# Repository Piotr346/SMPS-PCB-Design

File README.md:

# SMPS-PCB-Design
Switch-mode power supply design

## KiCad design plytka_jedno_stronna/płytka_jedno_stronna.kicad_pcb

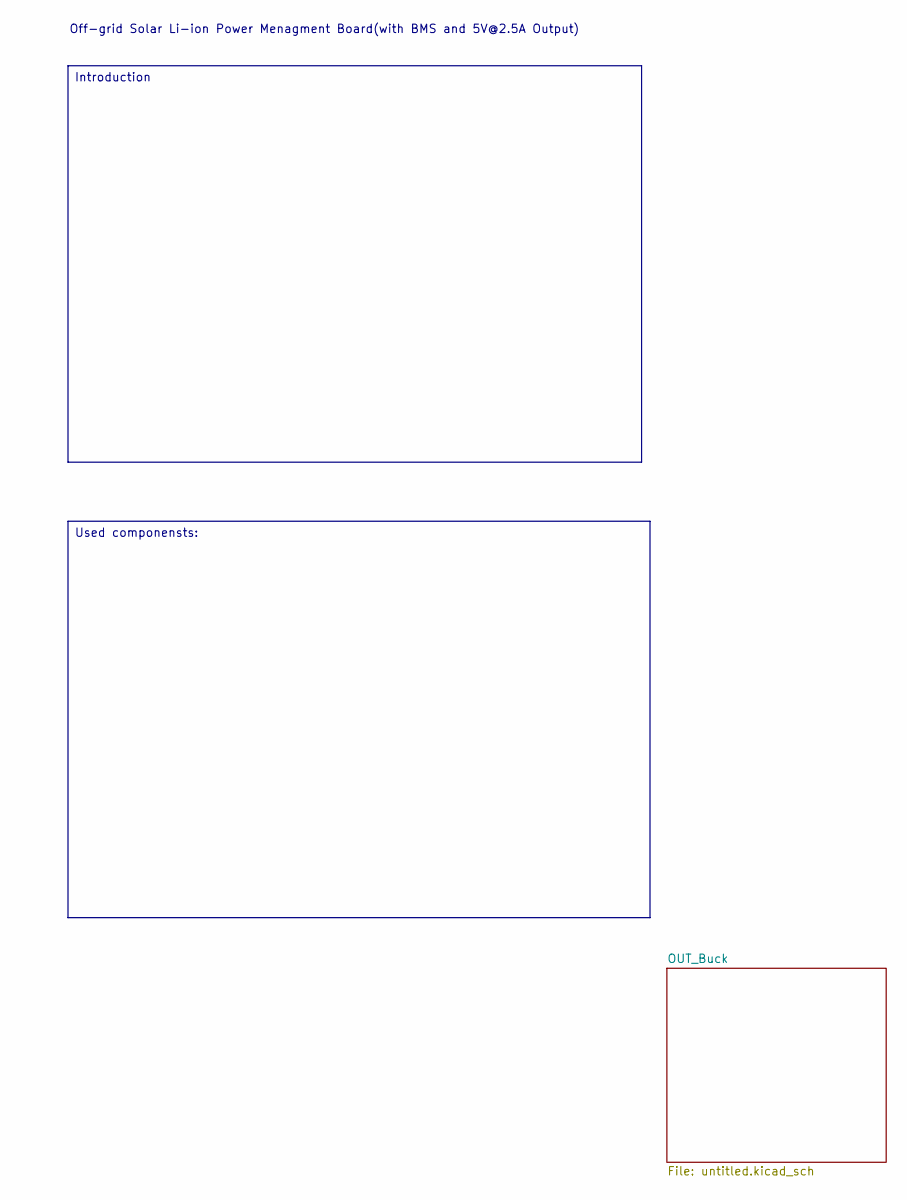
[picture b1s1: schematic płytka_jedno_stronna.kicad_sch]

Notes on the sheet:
Off-grid Solar Li-ion Power Menagment Board(with BMS and 5V@2.5A Output)
Introduction
Used componensts:

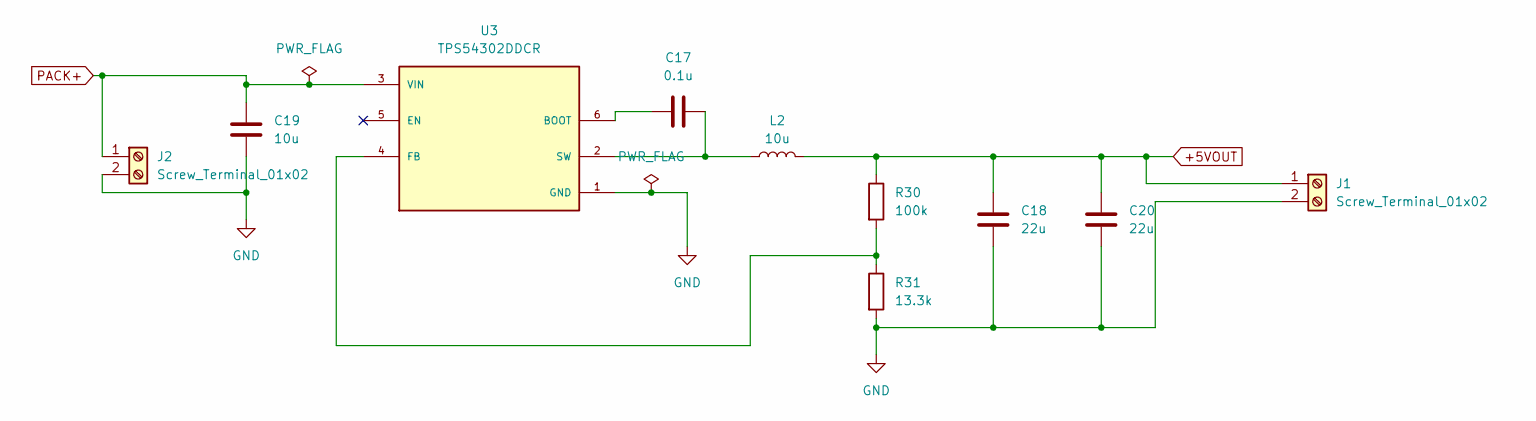
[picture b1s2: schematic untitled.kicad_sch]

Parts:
C17: 0.1u; C_1206_3216Metric_Pad1.33x1.80mm_HandSolder
C18, C20: 22u; C_1206_3216Metric_Pad1.33x1.80mm_HandSolder
C19: 10u; C_1206_3216Metric_Pad1.33x1.80mm_HandSolder
J1, J2: Screw_Terminal_01x02; TerminalBlock_Phoenix_PT-1,5-2-5.0-H_1x02_P5.00mm_Horizontal
L2: 10u; L_Vishay_IHLP-2525
R30: 100k; R_1206_3216Metric_Pad1.30x1.75mm_HandSolder
R31: 13.3k; R_1206_3216Metric_Pad1.30x1.75mm_HandSolder
U3: TPS54302DDCR; SOT-23-6; PARTREV A

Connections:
+5VOUT: C18.1, C20.1, J1.1, L2.2, R30.1
GND: C18.2, C19.2, C20.2, J1.2, J2.2, R31.2, U3.1 (GND)
unnamed: C17.1, U3.6 (BOOT)
unnamed: R30.2, R31.1, U3.4 (FB)
unnamed: C17.2, L2.1, U3.2 (SW)
PACK+: C19.1, J2.1, U3.3 (VIN)

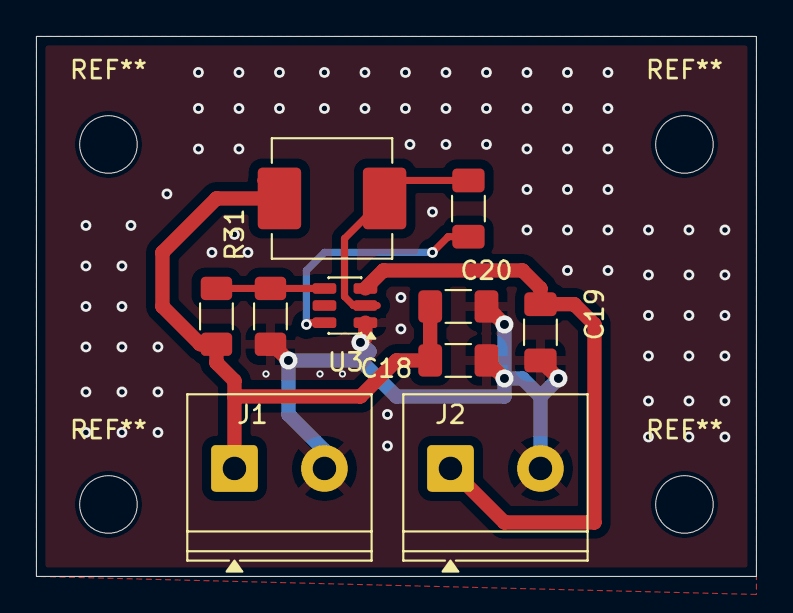
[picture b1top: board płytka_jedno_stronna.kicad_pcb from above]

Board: 2 copper layers, 40.0 x 30.0 mm, 10 parts (0 on the bottom side), 6 nets.

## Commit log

2026-03-28 Correct typo in project description
